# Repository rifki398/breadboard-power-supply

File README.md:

# Breadboard Power Supply
<table>
  <tr>
    <td align="center">
      
      <br/>3D View
    </td>
    <td align="center">
      
      <br/>PCB View
    </td>
  </tr>
</table>

## Description
This project is a simple PCB design using KiCad to provide regulated 5V and 3.3V outputs from an external DC power source (9-12V). The board uses a LM7805 linear regulator to generate 5V and a LD1117V regulator to generate 3.3V. The regulated outputs are available through pin headers and screw terminals, making the board suitable as a compact power module for prototyping on breadboards or external circuits.

## Bill of Materials (BOM)

| No. | Component                     | Quantity | Description / Value           | Package Type |
|-----|-------------------------------|----------|-------------------------------|--------------|
| 1   | LM7805                        | 1        | 5V Regulator                  | TO-220       |
| 2   | LD1117V                       | 1        | 3.3V Voltage Regulator        | TO-220       |
| 3   | Slide Switch                  | 1        | On/Off switch                 | 3 pin 6x6x5  |
| 4   | Barrel Jack Connector         | 1        | DC input, 9–12 V              | THT          |
| 5   | LED                           | 1        | Power indicator               | 5 mm THT     |
| 6   | Capacitor (Electrolytic)      | 3        | 10uF (1x), 1uF (1x), 0.1uF (1x)   | Radial THT   |
| 7   | Resistor                      | 1        | 330R                          | Axial THT    |
| 8   | 01x02 Pinheader               | 2        | Output to the breadboard      | Male type    |
| 9   | 01x03 Pinheader               | 1        | Output switcher (5 & 3.3V)    | Male type    |
| 10  | 01x02 Screw Connector         | 3        | Input/output terminal         | -            |

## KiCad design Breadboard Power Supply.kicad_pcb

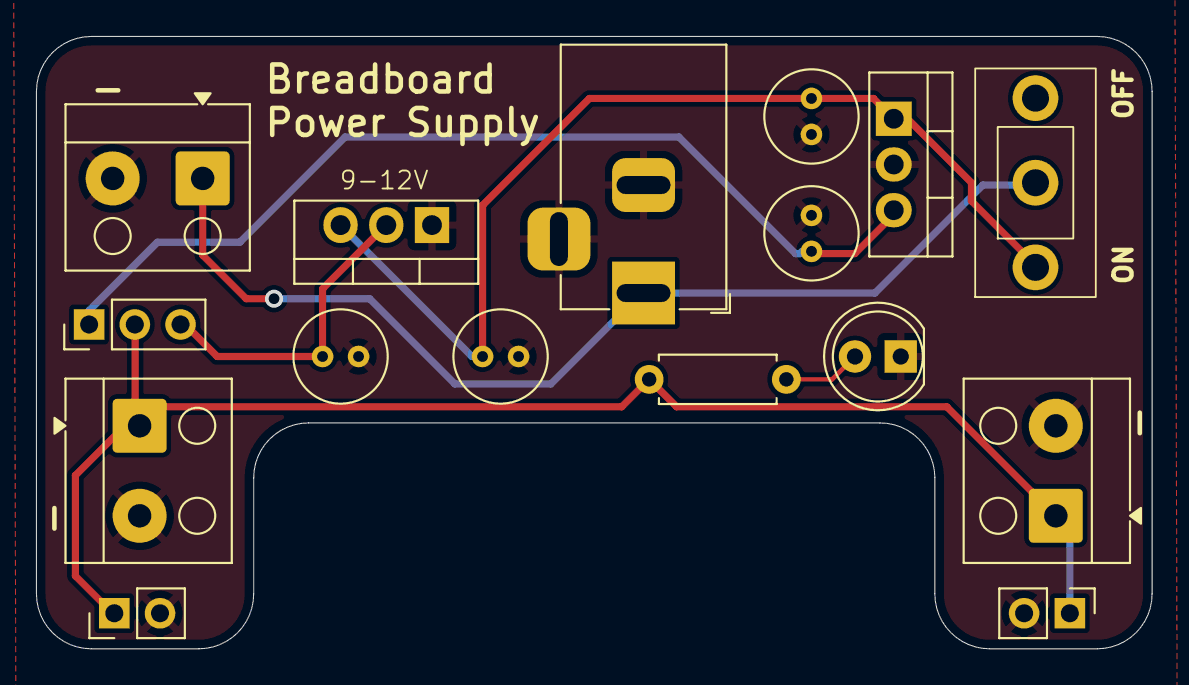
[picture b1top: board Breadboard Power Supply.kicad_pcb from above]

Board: 2 copper layers, 62.0 x 34.0 mm, 16 parts (0 on the bottom side), 7 nets.

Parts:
C1: 10u; C_Radial_D5.0mm_H5.0mm_P2.00mm
C2: 0.1; C_Radial_D5.0mm_H5.0mm_P2.00mm
C3: 1u; C_Radial_D5.0mm_H5.0mm_P2.00mm
C4: 0.1u; C_Radial_D5.0mm_H5.0mm_P2.00mm
D1: LED; LED_D5.0mm
J1: Barrel_Jack_Switch; BarrelJack_Horizontal
J2: Conn_01x03_Pin; PinHeader_1x03_P2.54mm_Vertical
J3, J4: Conn_01x02_Pin; PinHeader_1x02_P2.54mm_Vertical
J5, J6, J7: Screw_Terminal_01x02; Altech_AK100_1x02_P5.00mm
R1: 330; R_Axial_DIN0207_L6.3mm_D2.5mm_P7.62mm_Horizontal
SW1: SS12D10; SS12D10_THT_12.7x6.7mm_P4.7mm
U1: LM7805_TO220; TO-220-3_Vertical
U2: LD1117V; TO-220-3_Vertical

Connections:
/3V3: C4.1, J2.3, U2.2 (VO)
/5V: C2.1, J2.1, U1.3 (VO)
/VI: C1.1, C3.1, SW1.1, U1.1 (VI), U2.3 (VI)
GND: C1.2, C2.2, C3.2, C4.2, D1.1 (K), J1.2, J1.3, J3.2, J4.2, J5.2, J6.2, J7.2, U1.2 (GND), U2.1 (GND)
unnamed: D1.2 (A), R1.2
unnamed: J2.2, J3.1, J4.1, J5.1, J6.1, R1.1
unnamed: J1.1, J7.1, SW1.2

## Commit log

2025-09-11 Rename picture/Breadboard Power Supply.png to 3dview.png
2025-09-11 Rename 3dview.png to picture/3dview.png
